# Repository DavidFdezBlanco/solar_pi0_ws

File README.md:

# Documentation
description of the project --> TODO

## RFM95W HopeRF breakout pinout
    RFM95W      GPIO        Pin_GPIO
    Vin                     17        
    GND                     25        
    EN          NC          NC
    GO          22          15
    SCK         11          23
    MISO        09          21
    MOSI        10          19
    CS          08          24
    RST         25          22

## BME680 sensor breakout pinout
    BME680      GPIO        Pin_GPIO
    3V                      1
    GND                     09
    SCK         03          05        
    SDO         NC          NC
    SDI         02          03
    CS          NC          NC

# Manual install
This project has been tested on Raspbian Jessie and Raspbian Stretch.
At first, in order to comunicate between Pi-Platter board and Raspberry Pi Zero W, we have to install two utility programs.
To install these programs, we have to open utility folder and follow the instructions written in readme.cmd file.

## Dependencies install for sensor and HopeRF
In order to use BME680 sensor and LoRaWAN HopeRF RFM95M with Raspebbry Pi Zero W, we have to install SPI and I2C port drivers at first and, then, install BME680 and RFM95W  libraries in dist-package of our raspbian distribution.

    sudo apt-get update
    sudo apt-get install i2c-tools python3-smbus python3-spidev python3-setuptools

Let's go to Adafruit_CircuitPython_BME680-master folder and launch

    sudo python3 setup.py install

Let's go to Adafruit_CircuitPython_TinyLoRa-master folder and launch

    sudo python3 setup.py install

We can test these two devices by going in examples folder. Different scripts are proposed by Adafruit CircuitPython libraries.

In lora_prj folder, we  can see two scripts:

    pi_bme680.py --> test if data are sent to TTN
    pi_talkpp.sh --> script of this project with communication with Pi_Platter board

The pi_talkpp.sh script is designed to be run by /etc/rc.local when the Pi Zero boots.  It looks at the power-up reason and does not execute if the Pi was powered on because the user powered up using the Solar Pi Platter button.

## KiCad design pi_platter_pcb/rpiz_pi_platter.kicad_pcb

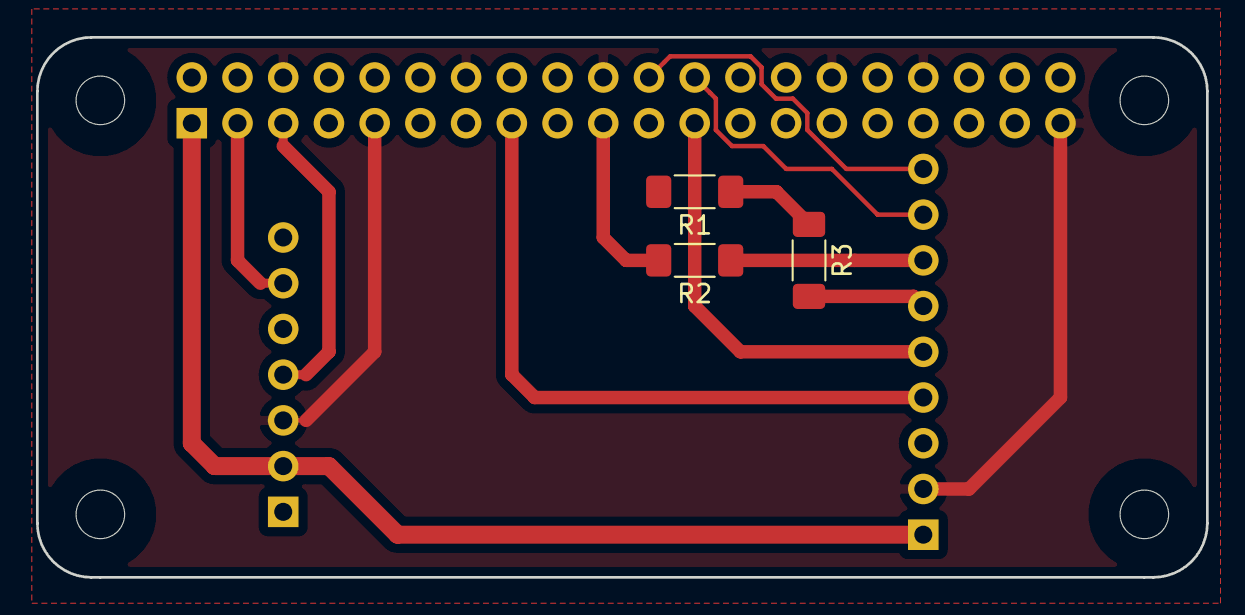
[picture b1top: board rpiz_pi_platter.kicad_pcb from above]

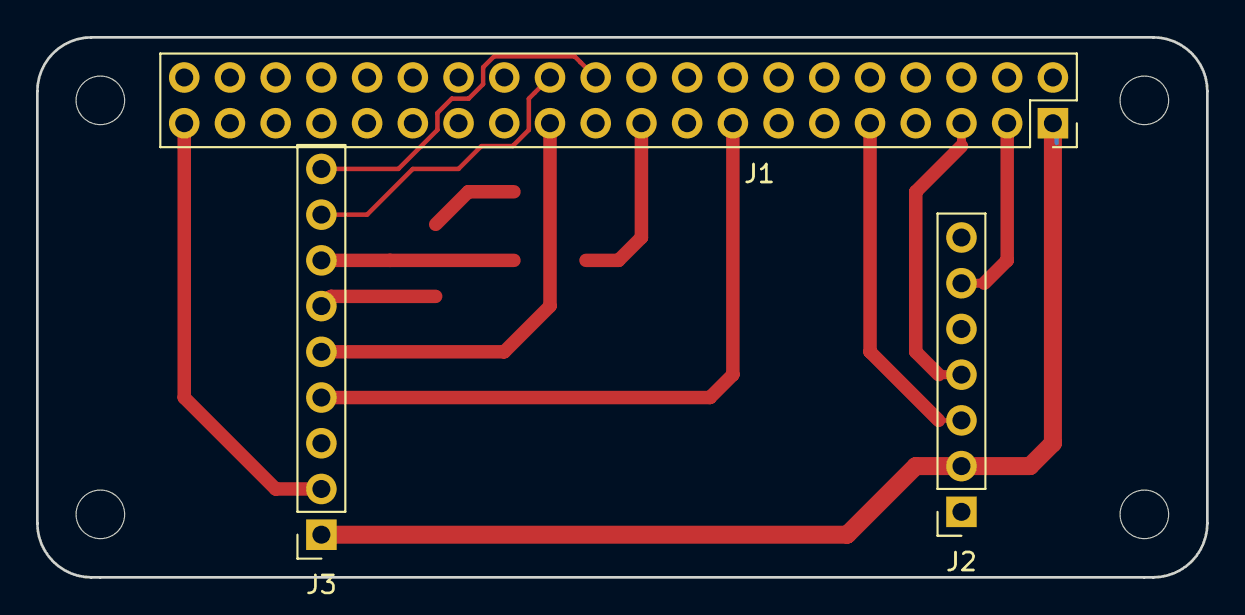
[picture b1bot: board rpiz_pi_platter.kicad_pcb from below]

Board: 2 copper layers, 65.0 x 30.0 mm, 10 parts (3 on the bottom side), 14 nets.

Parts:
H1, H2, H3, H4: MountingHole; MountingHole_2.7mm_M2.5_uHAT_RPi
J1: GPIO_CONNECTOR; PinSocket_2x20_P2.54mm_Vertical_Centered_Anchor
J2: BME680_CONNECTOR; PinSocket_1x07_P2.54mm_Vertical
J3: RFM95W_CONNECTOR; PinSocket_1x09_P2.54mm_Vertical
R1, R2, R3: R; R_1806_4516Metric

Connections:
+3V3: J1.1, J1.17, J2.2, J3.1
+5V: J1.2, J1.4
/GPIO2_SDA1: J1.3, J2.6
/GPIO3_SCL1: J1.5, J2.4
/GPIO8_SPI_CE0_N: J1.24, J3.8
/GPIO9_SPI_MISO: J1.21, R1.2
/GPIO10_SPI_MOSI: J1.19, R2.2
/GPIO11_SPI_SCLK: J1.23, J3.5
/GPIO22_GEN3: J1.15, J3.4
/GPIO25_GEN6: J1.22, J3.9
GND: J1.6, J1.9, J1.14, J1.20, J1.25, J1.30, J1.34, J1.39, J2.3, J3.2
unnamed: J3.6, R3.2
unnamed: J3.7, R2.1
unnamed: R1.1, R3.1

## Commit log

2019-09-17 technical documentation of solar panel weather station borad
2019-09-17 utility programs to simplify the communication with solar pi_platter board
2019-09-17 solar pi_platter test without sensor and LoRa module
2019-09-24 pi_platter bme680 project written in python code
2019-09-27 raspberry pi zero w GPIO pinout
2019-10-02 pi platter project on python and linux shell script install
2019-10-03 sensor and Lora HopeRF test
2019-10-07 modification of linux shell script
2019-10-08 new lora script to send packet
2019-10-08 debug pi_talkpp
2019-10-08 debug and shell script install
2019-10-08 debug error command in same line
2019-10-16 edit readme to install dependencies
2019-10-16 edit readme install file
2019-10-18 modification of low voltage threshold in linux script shell file
2019-10-21 disable version test of adafruit-tiny-lora.py driver
2019-10-22 modification of ground plane
2019-10-25 modification of TIMELAPSE and TIMELOWBATT variables values (30 mins and 10 mins)
2019-10-25 add comments in shell script
2019-11-08 add freecad files in order to make pi platter box
2019-11-14 modification of pcb

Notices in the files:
pi_platter_pcb/rpiz_pi_platter.kicad_pcb:
This PCB design is licensed under MIT Open Source License.
